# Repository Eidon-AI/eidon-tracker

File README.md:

# Eidon Tracker

A complete Bluetooth IMU tracking system featuring custom hardware, 3D printed enclosure, and web-based applications. The Eidon Tracker transmits real-time quaternion orientation data over Bluetooth HID, making it perfect for motion capture, gaming, and interactive applications.

<div align="center">
  
</div>

## Features

- **High-precision IMU tracking** with BNO085 9-DOF sensor
- **Bluetooth HID device** - appears as standard input device
- **Real-time quaternion data** streaming at 1000Hz
- **Custom 3D printed enclosure** with integrated switches
- **Web-based applications** for visualization and interaction
- **Battery monitoring** with charging status
- **Device color customization** via HID feature reports

## Bill of Materials (BOM)

<div align="center">
  
</div>

### Required Components

| Component | Quantity | Description | Purchase Link |
|-----------|----------|-------------|---------------|
| [Seeed XIAO ESP32-C6](https://www.seeedstudio.com/Seeed-XIAO-ESP32C6-p-5884.html) | 1 | Main microcontroller with built-in BLE 5 and WiFi 6 | [Seeed Studio](https://www.seeedstudio.com/Seeed-XIAO-ESP32C6-p-5884.html) |
| BNO085 IMU Breakout | 1 | 9-DOF Absolute Orientation Sensor | [Amazon](https://amzn.to/4mKZSTC) |
| LiPo Battery (3.7V) | 1 | 250mAh recommended | [Amazon](https://amzn.to/4kpmNSK) |
| Toggle Switches (6mm) | 2 | For power and position config | [Amazon](https://amzn.to/3ZfAECM) |
| 30 AWG Wires | 7x ~5cm | Female-to-female, ~20cm | [Amazon](https://amzn.to/4kB8Z7V) |

### 3D Printing Materials

| Material | Quantity | Description |
|----------|----------|-------------|
| PLA Filament | ~50g | For enclosure parts |
| Support Material | As needed | If printing with overhangs |

### Tools Required

- 3D Printer
- Soldering iron and solder
- Small screwdriver
- Wire strippers

**Estimated Total Cost**: $80-120 USD

## Hardware Setup

### Wiring Diagram

Connect the BNO085 to the XIAO ESP32-C6 using SPI interface:

| BNO085 Pin | XIAO ESP32-C6 Pin | GPIO | Function |
|------------|-------------------|------|----------|
| VIN | 3V3 | - | Power (3.3V) |
| GND | GND | - | Ground |
| CS | D1 | GPIO17 | SPI Chip Select |
| SCK/SCL | D2 | GPIO19 | SPI Clock |
| MOSI/DI | D3 | GPIO18 | SPI Master Out |
| MISO/SDA | D4 | GPIO20 | SPI Master In |
| INT | D5 | GPIO22 | Interrupt |
| RST | D6 | GPIO23 | Reset |
| WAK | D0 | GPIO2 | Wake (optional) |

### Switch Connections

| Switch | Output Pin | Input Pin | Function |
|--------|------------|-----------|----------|
| Left/Right | D7 | D8 | Horizontal orientation |
| Upper/Lower | D9 | D10 | Vertical orientation |

### 3D Printing

Print the following files from the `cad/` directory:

1. `eidon-tracker-base.stl` - Main enclosure base
2. `eidon-tracker-top.stl` - Enclosure lid  
3. `eidon-tracker-mount.stl` - Optional mounting bracket

**Print Settings:**
- Layer Height: 0.2mm
- Infill: 20%
- Support: Yes (for overhangs)
- Material: PLA

## Software Setup

### ESP-IDF Installation

1. Install ESP-IDF v6.0 or later:
   ```bash
   # macOS/Linux
   mkdir -p ~/esp
   cd ~/esp
   git clone -b v6.0 --recursive https://github.com/espressif/esp-idf.git
   cd esp-idf
   ./install.sh esp32c6
   . ./export.sh
   ```

   For Windows, follow the [ESP-IDF Windows Installer guide](https://docs.espressif.com/projects/esp-idf/en/latest/esp32/get-started/windows-setup.html)

2. Install build dependencies:
   ```bash
   # Ubuntu/Debian
   sudo apt-get install git wget flex bison gperf python3 python3-pip python3-venv cmake ninja-build ccache libffi-dev libssl-dev dfu-util libusb-1.0-0
   
   # macOS
   brew install cmake ninja dfu-util
   ```

### Building and Uploading Firmware

1. Clone this repository:
   ```bash
   git clone https://github.com/yourusername/eidon-tracker.git
   cd eidon-tracker
   ```

2. Initialize submodules:
   ```bash
   git submodule update --init --recursive
   ```

3. Build the firmware:
   ```bash
   make build
   # or
   cd firmware
   . ~/esp-idf/export.sh
   idf.py build
   ```

4. Connect your XIAO ESP32-C6 via USB

5. Flash the firmware:
   ```bash
   make flash
   # or with monitor
   make flash-monitor
   ```

### Dependencies

The firmware uses the following ESP-IDF components:

- **bno08x_driver** - BNO085 SPI driver (included as submodule)
- **ESP-IDF Bluetooth Stack** - BLE functionality
- **FreeRTOS** - Real-time operating system

## Web Applications

The `web/` directory contains the main interactive application:

### 3D Orientation Visualizer (`index.html`)

- **Real-time 3D visualization** of tracker orientation and movement
- **Multiple camera angles** and viewing modes
- **Bluetooth HID integration** for seamless device connectivity
- **Calibration status monitoring** and quaternion data display

### Running Web Applications

Simply open `web/index.html` directly in your web browser:

1. Navigate to the `web/` directory in your file explorer
2. Double-click `index.html` to open it in your default browser
3. Or right-click and "Open with" your preferred browser (Chrome/Edge recommended for Web Bluetooth support)
4. Connect to your Eidon Tracker via Bluetooth

## HID Reports

The Eidon Tracker implements a custom HID device with multiple report types for data exchange:

### Input Report (Report ID: 1)
**Size**: 9 bytes total
- **Quaternion Data** (8 bytes): Four 16-bit values representing orientation
  - `w` component (bytes 0-1): Scalar part of quaternion
  - `x` component (bytes 2-3): X-axis rotation
  - `y` component (bytes 4-5): Y-axis rotation  
  - `z` component (bytes 6-7): Z-axis rotation
- **Switch States** (1 byte): Two button states plus padding
  - Bit 0: Left/Right switch state
  - Bit 1: Upper/Lower switch state
  - Bits 2-7: Reserved (padding)

### Output Report (Report ID: 1)
**Size**: 1 byte
- **Vendor Command**: Custom command byte for device control
  - Used for device configuration and special commands
  - Values defined in firmware for various operations

### Feature Report (Report ID: 1)  
**Size**: 3 bytes
- **RGB Color Settings**: Device LED color configuration
  - Byte 0: Red component (0-255)
  - Byte 1: Green component (0-255)
  - Byte 2: Blue component (0-255)
  - Colors are stored in device flash memory
  - Allows customization of device LED color

### HID Usage Pages
- **Primary**: Sensor Page (0x20) - Orientation Usage (0x80)
- **Secondary**: Button Page (0x09) - Button 1-2
- **Vendor**: Custom Page (0xFF00) - Vendor-specific features

## Usage

### Initial Setup

1. **Power on** the device - LED will indicate status
2. **Pair via Bluetooth** - Device appears as "Eidon Tracker XXXX"
3. **Calibrate IMU** - Wave device in figure-8 pattern until calibrated
4. **Open web application** of choice
5. **Connect** to device in web browser

### Calibration Process

The BNO085 sensor requires calibration for optimal performance:

1. **Gyroscope**: Keep device stationary for 2-3 seconds
2. **Accelerometer**: Slowly rotate through all orientations  
3. **Magnetometer**: Move device in figure-8 pattern away from magnetic interference
4. Monitor calibration status in web application or serial output

### LED Status Indicators

| LED State | Meaning |
|-----------|---------|
| Solid Blue | Connected and ready |
| Blinking Blue | Advertising/pairing mode |
| Red | Low battery or error |
| Green | Charging |

## Development

### Project Structure

```
eidon-tracker/
├── firmware/              # ESP-IDF firmware project
│   ├── main/             # Main application source
│   ├── components/       # Custom components
│   │   └── bno08x_driver/ # BNO085 SPI driver submodule
│   ├── CMakeLists.txt    # CMake configuration
│   └── sdkconfig.defaults # Default configuration
├── web/                   # Web applications
│   ├── index.html         # 3D orientation visualizer
│   └── script.js          # Shared JavaScript libraries
├── cad/                   # 3D printing files
│   ├── eidon-tracker.f3d  # Fusion 360 source
│   ├── *.stl              # STL files for printing
│   └── *.gcode            # Pre-sliced files
├── images/                # Product photos
├── Makefile               # Root build automation
└── README.md              # This file
```

### Firmware Development

The firmware is built on ESP-IDF v6.0 with FreeRTOS. Key components:

- **HID Report Descriptor**: Custom HID device with quaternion data
- **Bluetooth Stack**: ESP-IDF BLE implementation
- **SPI IMU Driver**: High-speed BNO08x driver for reliable communication
- **Battery Management**: Built-in XIAO charging and monitoring

### Build Commands

The root Makefile provides convenient commands:

```bash
make build              # Build the firmware
make flash              # Flash the firmware to device
make monitor            # Open serial monitor
make clean              # Clean build files
make fullclean          # Full clean (remove all build artifacts)
make menuconfig         # Open ESP-IDF configuration menu
make flash-monitor      # Flash and then monitor
make build-flash        # Build and flash
make build-flash-monitor # Build, flash, and monitor
```

### Adding New Web Applications

1. Create new HTML file in `web/` directory
2. Include `script.js` for Bluetooth connectivity
3. Implement HID report parsing for quaternion data
4. Add visualization or interaction logic

## Troubleshooting

### Connection Issues

- **Device not found**: Ensure Bluetooth is enabled and device is in pairing mode
- **Connection drops**: Check battery level and distance from host device
- **Web Bluetooth not supported**: Use Chrome/Edge on desktop or Android

### Calibration Problems

- **Poor tracking accuracy**: Ensure proper IMU calibration
- **Drift over time**: Recalibrate magnetometer away from metal objects
- **Erratic behavior**: Check SPI wiring connections and signal integrity

### Build Issues

- **Target mismatch**: Run `make fullclean` then `make build` to ensure ESP32-C6 target
- **Submodule missing**: Run `git submodule update --init --recursive`
- **ESP-IDF not found**: Ensure you've sourced `~/esp-idf/export.sh`
- **Upload fails**: Hold BOOT button while connecting USB, then release

## Contributing

1. Fork the repository
2. Create a feature branch
3. Make your changes
4. Test thoroughly
5. Submit a pull request

## License

This project is open source and available under the MIT License. See LICENSE file for details.

## Acknowledgments

- [Seeed Studio](https://www.seeedstudio.com/) for the excellent XIAO nRF52840 Sense board
- [Adafruit](https://www.adafruit.com/) for comprehensive sensor libraries and breakout boards
- [PlatformIO](https://platformio.org/) for the excellent development environment

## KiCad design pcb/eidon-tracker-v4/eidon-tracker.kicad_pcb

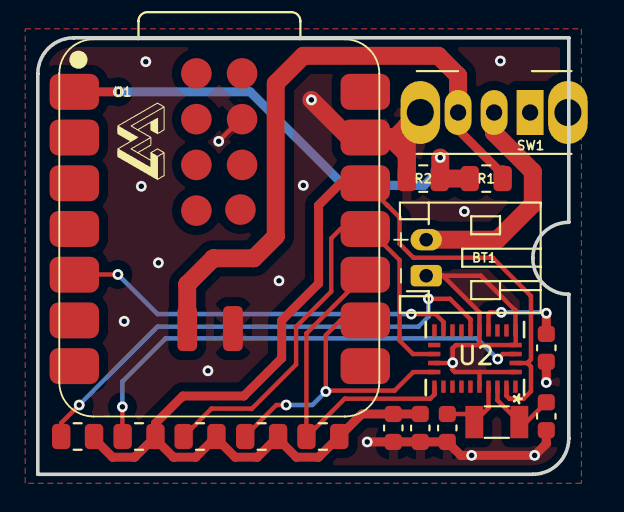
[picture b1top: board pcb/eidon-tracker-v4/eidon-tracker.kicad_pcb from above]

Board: 2 copper layers, 29.5 x 24.2 mm, 19 parts (1 on the bottom side), 14 nets.

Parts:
BT1: Battery; JST_PH_S2B-PH-K_1x02_P2.00mm_Horizontal_Inversed
C1, C2: 22pF; C_0603_1608Metric
C3, C4, C5: 100nF; C_0603_1608Metric
G1, G1#2: LOGO
R1, R2: 220kΩ; R_0805_2012Metric
R3, R4: 2.2kΩ; R_0805_2012Metric
R5, R6, R7: 10kΩ; R_0805_2012Metric
SW1: SW_SPDT; SW_Slide_SPDT_Angled_CK_OS102011MA1Q
U1: XIAO-ESP32-C6; XIAO-ESP32C6-SMD
U2: BNO085
X1: 32.768KHz; Crystal_SMD_3215-2Pin_3.2x1.5mm

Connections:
/BAT_EXT: BT1.1 (+), SW1.2 (B)
/BAT_INT: R1.2, SW1.3 (C), U1.15 (BAT)
/BAT_LVL: R1.1, R2.1, U1.1 (GPIO0_A0_D0)
/BOOTN: R5.1, U2.4 (BOOTN)
/CAP: C3.2, U2.9 (CAP)
/INT: U1.5 (GPIO22_D4_SDA), U2.14 (H_INTN)
/RST: R6.1, U2.11 (NRST)
/SCL: R3.1, U1.9 (GPIO19_D8_SCK), U2.19 (H_SCL/SCK/RX)
/SDA: R4.1, U1.10 (GPIO20_D9_MISO), U2.20 (H_SDA/H_MISO/TX)
/SDO: R7.1, U1.11 (GPIO18_D10_MOSI), U2.17 (SA0/H_MOSI)
/XIN: C1.2, U2.27 (XIN32), X1.1
/XOUT: C2.2, U2.26 (XOUT32/CLKSEL1), X1.2
GND: BT1.2 (-), C1.1, C2.1, C3.1, C4.1, C5.1, R2.2, SW1.4 (S), U1.13 (GND), U1.16 (GND), U1.20 (GND), U2.2 (GND), U2.5 (PS1), U2.6 (PS0/WAKE), U2.10 (CLKSEL0), U2.18 (H_CSN), U2.25 (GND)
VCC: C4.2, C5.2, R3.2, R4.2, R5.2, R6.2, R7.2, U1.12 (3V3), U2.3 (VDD), U2.28 (VDDIO)

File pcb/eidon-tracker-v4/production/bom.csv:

Designator,Footprint,Quantity,Value,LCSC Part #
BT1,JST_PH_S2B-PH-K_1x02_P2.00mm_Horizontal_Inversed,1,Battery,
"C1, C2",0603,2,22pF,
"C3, C4, C5",0603,3,100nF,
"R1, R2",0805,2,220K,
"R3, R4",0805,2,2.2K,
"R5, R6, R7",0805,3,10K,
SW1,SW_Slide_SPDT_Angled_CK_OS102011MA1Q,1,SW_SPDT,
U1,XIAO-ESP32C6-SMD,1,XIAO-ESP32-C6,
U2,BNO085,1,BNO085,
X1,Crystal_SMD_3215-2Pin_3.2x1.5mm,1,32.768KHz,

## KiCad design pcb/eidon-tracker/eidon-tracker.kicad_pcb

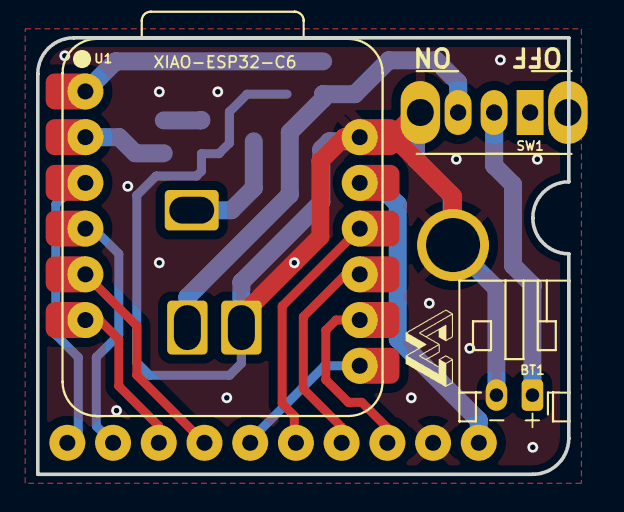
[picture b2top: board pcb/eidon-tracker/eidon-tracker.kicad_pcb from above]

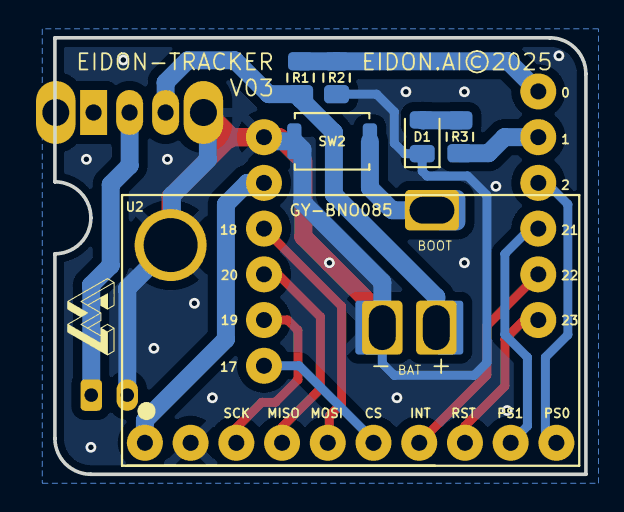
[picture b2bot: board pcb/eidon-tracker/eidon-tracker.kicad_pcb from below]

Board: 2 copper layers, 29.5 x 24.2 mm, 11 parts (7 on the bottom side), 16 nets.

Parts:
BT1: Battery; JST_PH_S2B-PH-K_1x02_P2.00mm_Horizontal
D1: LED; LED_0805_2012Metric
G1, G1#2: LOGO
R1, R2: 220k; R_0805_2012Metric
R3: 1.8k; R_0805_2012Metric
SW1: SW_SPDT; SW_Slide_SPDT_Angled_CK_OS102011MA1Q
SW2: SW_Push; SW_Push_SPST_NO_Alps_SKRK
U1: XIAO-ESP32-C6
U2: GY-BNO085

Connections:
/BAT_EXT: BT1.1 (+), SW1.2 (B)
/BAT_INT: R1.2, SW1.3 (C), U1.15 (BAT)
/BAT_LVL: R1.1, R2.1, U1.1 (GPIO0_A0_D0)
/BOOT: SW2.1, U1.23 (BOOT)
/CS: U1.8 (GPIO17_D7_RX), U2.6 (CS)
/INT: U1.5 (GPIO22_D4_SDA), U2.7 (INT)
/LED: R3.2, U1.2 (GPIO1_A1_D1)
/MISO: U1.10 (GPIO20_D9_MISO), U2.4 (SDA)
/MOSI: U1.11 (GPIO18_D10_MOSI), U2.5 (ADD)
/PS0: U1.3 (GPIO2_A2_D2), U2.10 (PS0)
/PS1: U1.4 (GPIO21_D3), U2.9 (PS1)
/RST: U1.6 (GPIO23_D5_SCL), U2.8 (RST)
/SCK: U1.9 (GPIO19_D8_SCK), U2.3 (SCL)
GND: BT1.2 (-), D1.1 (K), R2.2, SW1.5 (S), SW2.2, U1.13 (GND), U1.16 (GND), U2.2 (GND), U2.12 (GND)
unnamed: D1.2 (A), R3.1
VCC: U1.12 (3V3), U2.1 (VCC)

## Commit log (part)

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2025-04-14 adds base tracker firmware for IMU to BT output
2025-04-22 updates firmware to return just quaternion values in HID report and adds README docs covering setup
2025-04-29 HID outputs quat, X,Y,Z, then W; attempts to add VID/PID pair
2025-04-30 updates BNO085 I2C pins for updated device shell
2025-04-30 attempts to fix battery level and vendor/product ID
2025-04-30 adds support for sensor position switches and reports their state on the HID report
2025-04-30 adds gcode used to print on eidon bambu office printer
2025-05-04 increases quaternion values resolution to 16-bit
2025-05-06 adds web visualizer
2025-05-06 revert HID descriptor
2025-05-10 updates cad model to include a strap mount for the tracker
2025-05-12 disables bunch of logs and implements double tap to soft restart the IMU
2025-05-13 updates HID descriptor to use proper HID usage code for sensor quaternion values
2025-05-13 fix reporting of vendor/product id for ble hid device
2025-05-13 cleans up dead code and resolves intellisense lint errors
2025-05-13 fix scan name advertised to show full 'Eidon Tracker' string; disabled tap to reset IMU for now
2025-05-14 implements unique BLE advertised name to easily tell devices apart; updates to use a common vendor/product id for eidon devices
2025-05-14 implements qspi external flash storage read/write for saving device specific config
2025-05-14 moves all firmware files into firmware folder and adds platformio shim to enable project detection from root dir
2025-05-15 color not colour
2025-05-15 adds custom pio patch for adds feature report support to Bluefruit's BLEHidGeneric service
2025-05-19 updates model so that Eidon logo's top is oriented towards trackers calculated forward vector which is reversed to match position of IMU within the eidon glove
2025-05-28 fix: correctly oriented IMU quaternion so that yaw North is forward of the device mounted 180 degrees around Z based on datasheet
2025-05-29 fix: try again.. corrects misorientation
2025-06-02 feat: disables BNO085 int pin check for now; at least until we have time to wire it up and test its impact
2025-06-02 chore: bumps version number of fimrware reported to host device
2025-06-04 updates 3d models with eidon logo in original orientation; updates readme images
2025-06-09 Add custom GATT service for iOS compatibility and comprehensive documentation
    Firmware Changes:
    - Add custom GATT service (UUID: E1D00001-8B5A-3E5B-9E23-4F9B5C91BBDE) alongside existing BLE HID
    - Implement GATT characteristics for iOS support:
    * Quaternion data (notify/read): Real-time IMU data with switch states
    * Calibration (write/read): Trigger IMU calibration remotely
    * Color (write/read): Set device RGB color persistently
2025-06-11 fix: corrects platformio config paths so project can run from root of repo
2025-06-24 feat: updates model base to not include extra pos switches; adds dot indicator for multiple top shells to indicate hard coded pos
2025-06-26 Finishing functionality migration to the esp32 board
2025-06-30 Refactoring color and BNO code
2025-06-30 Refactoring code callbacks
2025-06-30 adding device role
2025-07-02 Implementing polling system to detect role changes
2025-07-02 Adding basic hub client structure
2025-07-02 Implementing scanning
2025-07-02 Refactoring HUB Client structure
2025-07-10 chore: archives/moves original firmware to firmware-nrf for reference and preps for firmware-v2 esp-idf transistion
2025-07-11 chore: finish clean up for merge of new hybrid firmware repo
2025-07-11 updates readme
2025-07-14 Removing HID, adding child functionality, fixing naming, and adding services for hub communication
2025-07-16 tweak
2025-07-16 Fixing platform.io issue and hub quaternion update
2025-07-17 Working on polling updates
2025-07-21 Transitioning hub to child comms to ESP NoW
2025-07-22 Implemebting ESP-NOW communication between trackers
2025-07-24 Updating SCL pin
2025-07-24 Removing quaternion prints
2025-07-24 Reducing IMU polling rate to 60Hz
2025-07-28 Fixing ESP NOW initialization
2025-07-28 Eliminating child timeout
2025-07-29 Setting disconnect on child role resetting
2025-08-08 First version of disconnect detection
2025-08-12 Adding a generalist packet structure to ESP NOW comms
2025-08-12 Cleaning the GAT characteristic after calibration over ble
2025-08-14 Implementing tree-calibration system
2025-08-14 adding debug to calibration callback
2025-08-14 Fixing esp now callback issue to fix calibration
2025-08-28 feat: adds updated models and 3d print files for new tracker mount for arms and chest
2025-09-10 feat(pcb): creates kicad project and custom xiao esp32-c6 footprint for easy soldering of battery pads
2025-09-11 feat(pcb): implements battery connector and power switch toggle
2025-09-11 chore(pcb): cleans out kicad auto backups
2025-09-12 feat(pcb): further optimizations to PCB layout and implements boot/user button
2025-09-17 feat(pcb): commits all pending pcb improvements
2025-09-19 feat(pcb): implements button and led circuit with smd componenets; chore(pcb): cleans up schematic and adds group labels to make the parts easier to understand
2025-09-23 feat(pcb): generates gerber files for fabrication
2025-09-23 feat(pcb): adds BOM and pick-n-place pos files needed for PCBA
2025-09-23 feat(cad): updates chest mount with extended mid-section to fit on alternate chest mount harness
2025-09-24 Updating the timeout
2025-10-06 feat(pcb): creates STEP model for v3 PCB and creates archive of Fusion of new v3 PCB shell
2025-10-07 feat(pcb): builds out most of the base enclosure shell model for updated pcb
2025-10-08 feat(pcb): further fleshes out the eidon shell and adds base lid
2025-10-21 feat(pcb): adds updated enclosure with integrated mount and extra secure screwable lid
2025-10-22 feat(pcb): adds updated models for integrated tracker mount
2025-10-24 feat(firmware): add battery monitoring and dual LED support
    - Add battery monitoring module using ADC on GPIO0 (A0)
    - Implements voltage divider reading with 16-sample averaging
    - Battery presence detection (handles floating ADC when USB-only)
    - Calculates battery percentage for LiPo (3.0V-4.2V range)
    - Runs monitoring task every 5 seconds
    - Add second status LED on GPIO1 (A1)
2025-10-27 revert: remove PCB LED and resistor changes
    Revert PCB schematic changes from previous commit while keeping
    firmware changes intact. The LED circuit and resistor value updates
    will be applied in a future PCB revision.
2025-11-04 fix(pcb): adds corrected BOM for incorrect LED resistor value
2025-11-04 chore: adds proj overview whitepaper outline
2025-11-05 docs: add comprehensive technical whitepaper with hardware images
    - Add complete WHITEPAPER.md covering system architecture, hardware, firmware, and mathematical framework
    - Include 12 hardware images (CAD renders, PCB designs, photos, diagrams)
    - Add styled HTML version with custom CSS (dark purple accent theme)
    - Document BOM with actual production costs (.84/device, .87/system)
    - Add KiCad schematic in appendix
    - Update contact information and dates to November 2025
2025-11-14 Add ESP32-C3 glove build environment
    Add seeed_xiao_esp32c3 build environment to support glove hardware.
    Includes ESP32_C3_GLOVE build flag for conditional compilation.
2025-11-14 Configure BNO085 I2C GPIO pins for glove hardware
    Add conditional GPIO pin configuration for BNO085:
    - ESP32-C6 Tracker: SDA=GPIO20, SCL=GPIO19, 400kHz
    - ESP32-C3 Glove: SDA=GPIO21, SCL=GPIO20, 100kHz
    ESP32-C6 retains I2C_ADR pin for address selection.
    ESP32-C3 glove uses fixed 0x4B address (no ADR pin).
2025-11-14 Add MUX-based finger sensor library for ESP32-C3 glove
    Create FingerSensors library with:
    - CD74HC4067 multiplexer support (4 select pins + 1 ADC)
    - 16-channel Hall effect sensor reading
    - ADC averaging (3 samples) for noise reduction
    - Calibration storage in NVS (min/max values per sensor)
    - BLE encoding: 0.0-1.0 normalized → -1.0-1.0 → uint16
2025-11-14 Add finger sensor GATT characteristic and integration
    Implement complete finger sensor integration for ESP32-C3 glove:
    GATT Service:
    - Add FINGER_SENSOR_CHAR_UUID (E1D0000A)
    - 32-byte characteristic (16 x uint16_t encoded values)
    - READ + NOTIFY properties
    - 50Hz update rate (same as quaternion)
2025-11-14 Add battery optimization note for IMU polling rate
2025-11-14 Update integration plan with Phase 1 completion status
    Mark all Phase 1 tasks as complete:
    - ESP32-C3 build environment ✅
    - BNO085 I2C configuration (100kHz both platforms) ✅
    - Glove roles (LEFT_GLOVE, RIGHT_GLOVE) ✅
    - FingerSensors library (MUX-based) ✅
    - GATT finger characteristic ✅
2025-11-14 docs: organize whitepaper files into dedicated folder
2025-11-24 Adding parition and small changes to .ini
2025-11-25 feat: add ESP32-C3 glove support with BLE-only mode
    - Skip Wire.begin() on C3 to prevent watchdog reset (I2C GPIO issue)
    - Disable WiFi/ESP-NOW initialization on C3 (BLE coexistence issue)
    - Add ESP32_C3_GLOVE conditional compilation throughout codebase
    - Use esp_mac.h instead of WiFi.h for MAC address on C3
    - Add finger sensor placeholder support for glove hardware
    - C3 glove boots successfully and is visible via BLE
2025-11-25 fix: enable LED on ESP32-C3 glove (GPIO5)
    - Add platform-specific LED pin definitions (C3: GPIO5, C6: GPIO15)
    - Remove C3-specific guards from LED code now that correct pin is used
    - C3 glove LED now blinks properly during advertising/connection
2025-11-25 feat: complete ESP32-C3 glove integration
    - Add default glove role (ROLE_LEFT_GLOVE) for C3 builds
    - Fix role validation to accept glove roles (8, 9)
    - Enable IMU support with correct I2C pins (SDA=21, SCL=20)
    - Use Wire.begin(SDA, SCL) method for C3 I2C initialization
2025-11-26 Fix finger sensor calibration to match eidon-glove implementation
    - Add polynomial coefficients from eidon-glove for raw ADC to proto_angle conversion
    - Add per-joint angle adjustment functions (MCP flexion, PIP flexion, abduction, thumb CMC)
    - Add dynamic calibration that auto-updates min/max as user moves fingers
    - Add sensor inversion flags for magnets with reversed polarity
    - Add per-sensor offset adjustments for specific joints
    - Update getEncodedValues to map adjusted angles to 0-255 then scale to uint16 for GATT
2025-12-29 Adding new characteristics for raw data
2025-12-29 IMplementing compilable raw data implementation
2025-12-29 Adding changelog and versioning
2025-12-31 Fixing sampling rate for raw data
2026-01-08 Updating gitignore
2026-01-08 Stop tracking .vscode and .cache directories
2026-01-08 Fixing firmware version reporting
2026-01-08 Fixing BLE raw data comms
2026-01-09 Small fix to hubs trasmitting raw data
2026-01-11 Adding new patch to local builds
2026-01-12 MAJOR
2026-01-13 Firmware patch
2026-01-13 Local build
2026-01-30 Add PCB v3 design files
2026-01-30 Add chest mount CAD files
2026-01-30 Add PCB v4 design with onboard BNO085
    Fully fab-ready design with BNO085 integrated directly on the PCB.
2026-01-30 Add user button support on GPIO9
    Reads boot/user button with debounce. Logs press events.
    IMU reset call stubbed out for future use.
2026-02-05 feat(pcb): finishes wiring up base BNO085 component
2026-02-12 Child battery reporting
2026-02-16 Fixing version bump
2026-02-19 Latest
